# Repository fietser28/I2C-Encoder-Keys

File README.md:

<!--
  SPDX-FileCopyrightText: 2023 Jan Nieuwstad <jan.sources@nieuwstad.net>
  SPDX-License-Identifier: CERN-OHL-W-2.0
-->

# Introduction

This is simple design to connect a rotary encoder with pushbutton and 4 switches to an MCU using I2C. The design uses the common MCP23008 chip. The BOM is kept simple with as many common parts as possible. The encoder and switches have a small RC network in place for basic debouncing (you still need to handle this also in software).

The board breaks out 3V3 power input, GND, SCL, SDA, Interrupt and !Reset.

The board provides pull up resistors for SCL, SDA and the !RESET pin. For each of them there also is a jumper to disable them.

NOTE: The rendering above has an encoder with round shaft, the knob is for an encoder with a D shaped shaft.

This board can be daisy chained. You just have to make sure each board uses a different addres by changing the jumpers A0,A1 and/or A2. Make sure you use the opendrain configuration of the interrupt pin if you want to use interrupts in this case.

# Files

 - The directory I2C-Encoder-Keys contains the KiCad (6) design files.
 - The BOM directory contains an bill of material generated by KiCad
 - 3D contains FreeCad design and 3D printable files (STL) for a case.
 - The root directory contains PDF of the schematic and PCB design.

# License 

This hardware design is under the [CERN Open Hardware Licence Version 2 - Weakly Reciprocal](LICENSES/CERN-OHL-W-4.0.txt)
Illustrations are under the [CERN Open Hardware Licence Version 2 - Weakly Reciprocal](LICENSES/CC-BY-SA-4.0.txt)

This project contains 3D models from others:
- [JST PH connector](https://grabcad.com/library/jst-ph-2-0mm-connector-pack-through-hole-smt-ds1066-1) from Sig Elso <https://grabcad.com/sig.elso-1>
- [Rotary encoder](https://grabcad.com/library/ec11-rotary-encoder-with-switch-1) from Anthony Berkow <https://grabcad.com/anthony.berkow-1>

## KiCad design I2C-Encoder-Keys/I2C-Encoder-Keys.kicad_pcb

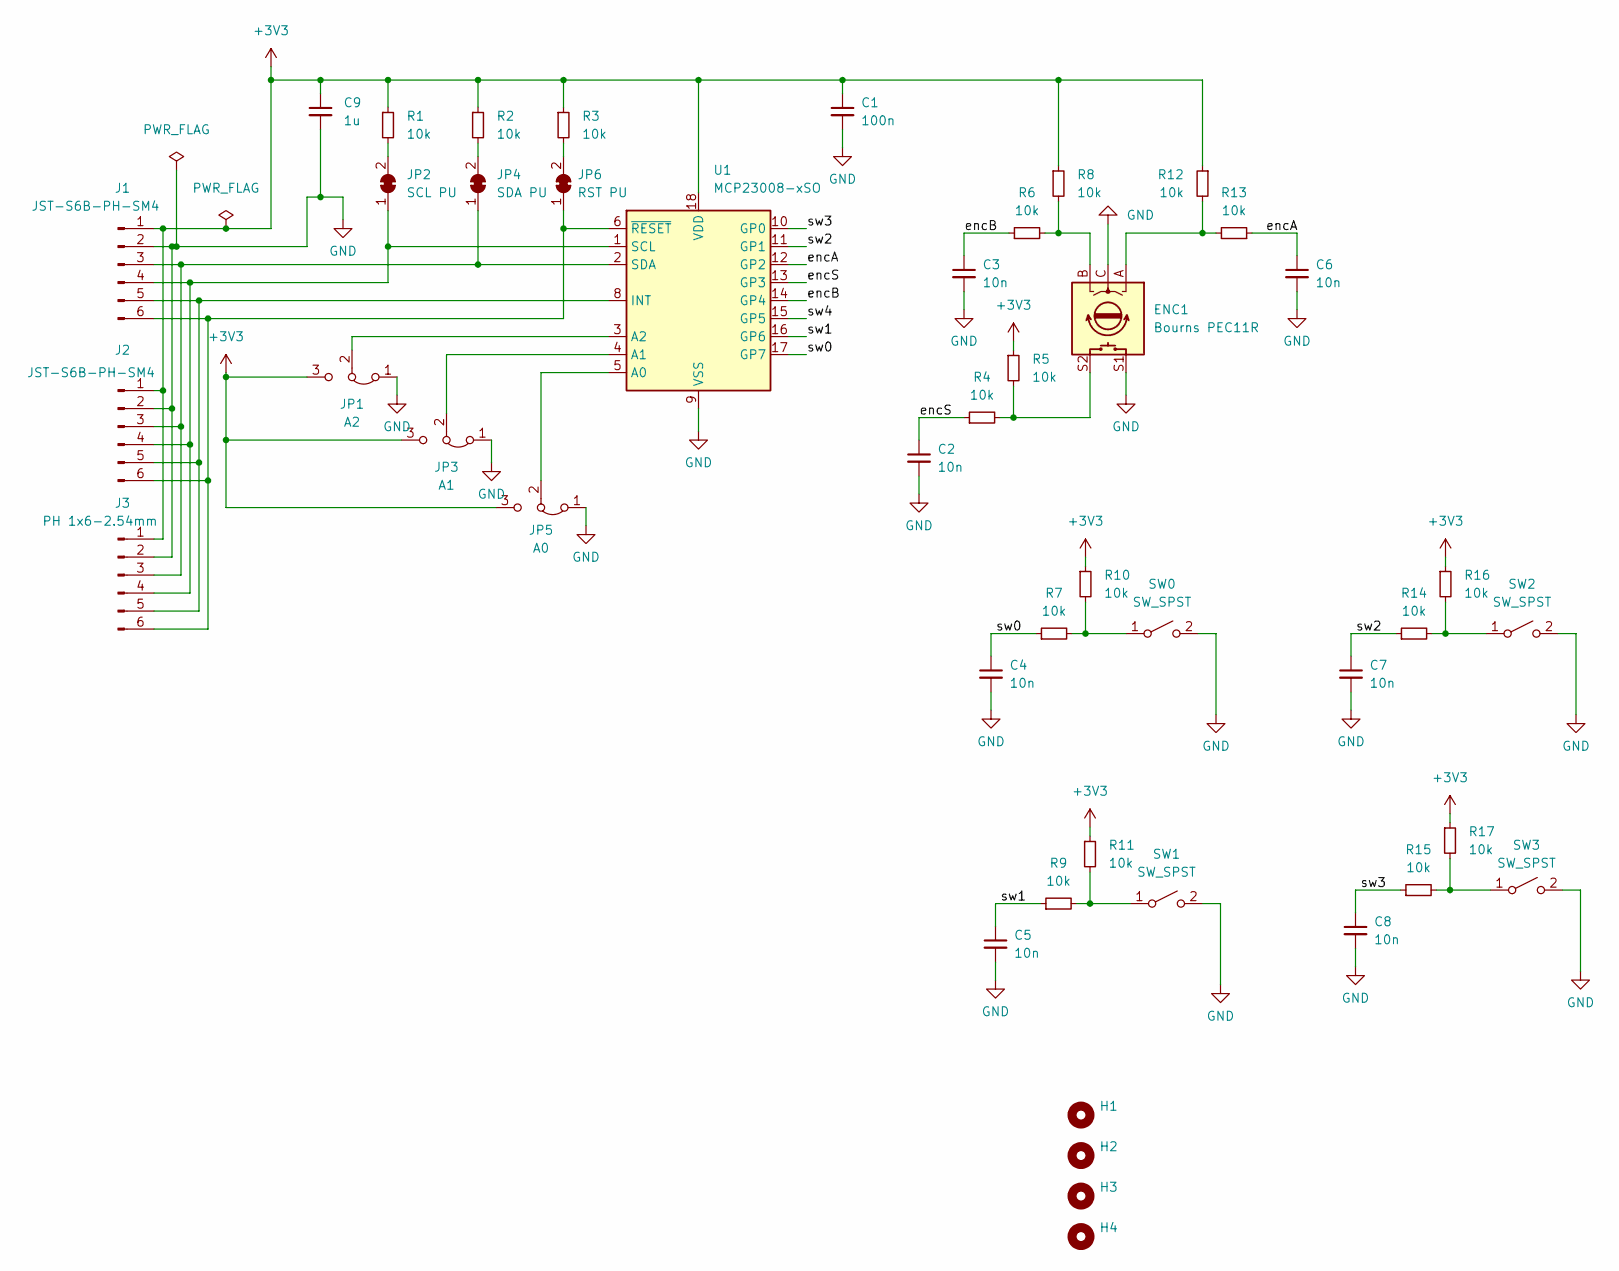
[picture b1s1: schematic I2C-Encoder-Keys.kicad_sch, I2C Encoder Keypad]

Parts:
C1: 100n; C_0805_2012Metric_Pad1.18x1.45mm_HandSolder; LCSC Part # C49678
C2, C3, C4, C5, C6, C7, C8: 10n; C_0805_2012Metric_Pad1.18x1.45mm_HandSolder; LCSC Part # C1710
C9: 1u; C_0805_2012Metric_Pad1.18x1.45mm_HandSolder; LCSC Part # C28323
ENC1: Bourns PEC11R; RotaryEncoder_Alps_EC12E-Switch_Vertical_H20mm
H1, H2, H3, H4: MountingHole; MountingHole_3.2mm_M3_Pad_Via
J1, J2: JST-S6B-PH-SM4; JST_PH_S6B-PH-SM4-TB_1x06-1MP_P2.00mm_Horizontal; LCSC Part # C265405
J3: PH 1x6-2.54mm; PinHeader_1x06_P2.54mm_Vertical
JP1: A2; SolderJumper-3_P1.3mm_Bridged12_RoundedPad1.0x1.5mm
JP2: SCL PU; SolderJumper-2_P1.3mm_Bridged_RoundedPad1.0x1.5mm
JP3: A1; SolderJumper-3_P1.3mm_Bridged12_RoundedPad1.0x1.5mm
JP4: SDA PU; SolderJumper-2_P1.3mm_Bridged_RoundedPad1.0x1.5mm
JP5: A0; SolderJumper-3_P1.3mm_Bridged2Bar12_RoundedPad1.0x1.5mm
JP6: RST PU; SolderJumper-2_P1.3mm_Bridged_RoundedPad1.0x1.5mm
R1, R2, R3, R4, R5, R6, R7, R8, R9, R10, R11, R12, R13, R14, R15, R16, R17: 10k; R_0805_2012Metric_Pad1.20x1.40mm_HandSolder; LCSC Part # C17414
SW0, SW1, SW2, SW3: SW_SPST; SW_PUSH_6mm_H9.5mm
U1: MCP23008-xSO; SOIC-18W_7.5x11.6mm_P1.27mm; LCSC Part # C92253

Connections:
+3V3: C1.1, C9.1, J1.1, J2.1, J3.1, JP1.3 (B), JP3.3 (B), JP5.3 (B), R1.1, R2.1, R3.1, R5.1, R8.1, R10.1, R11.1, R12.1, R16.1, R17.1, U1.18 (VDD)
/encA: C6.1, R13.1, U1.12 (GP2)
/encB: C3.1, R6.1, U1.14 (GP4)
/encS: C2.1, R4.1, U1.13 (GP3)
/sw0: C4.1, R7.1, U1.17 (GP7)
/sw1: C5.1, R9.1, U1.16 (GP6)
/sw2: C7.1, R14.1, U1.11 (GP1)
/sw3: C8.1, R15.1, U1.10 (GP0)
/sw4: U1.15 (GP5)
GND: C1.2, C2.2, C3.2, C4.2, C5.2, C6.2, C7.2, C8.2, C9.2, ENC1.C, ENC1.S1, J1.2, J2.2, J3.2, JP1.1 (A), JP3.1 (A), JP5.1 (A), SW0.2 (B), SW1.2 (B), SW2.2 (B), SW3.2 (B), U1.9 (VSS)
unnamed: ENC1.A, R12.2, R13.2
unnamed: ENC1.B, R6.2, R8.2
unnamed: ENC1.S2, R4.2, R5.2
unnamed: J1.3, J2.3, J3.3, JP4.1 (A), U1.2 (SDA)
unnamed: J1.4, J2.4, J3.4, JP2.1 (A), U1.1 (SCL)
unnamed: J1.5, J2.5, J3.5, U1.8 (INT)
unnamed: J1.6, J2.6, J3.6, JP6.1 (A), U1.6 (~RESET)
unnamed: JP1.2 (C), U1.3 (A2)
unnamed: JP2.2 (B), R1.2
unnamed: JP3.2 (C), U1.4 (A1)
unnamed: JP4.2 (B), R2.2
unnamed: JP5.2 (C), U1.5 (A0)
unnamed: JP6.2 (B), R3.2
unnamed: R7.2, R10.2, SW0.1 (A)
unnamed: R9.2, R11.2, SW1.1 (A)
unnamed: R14.2, R16.2, SW2.1 (A)
unnamed: R15.2, R17.2, SW3.1 (A)

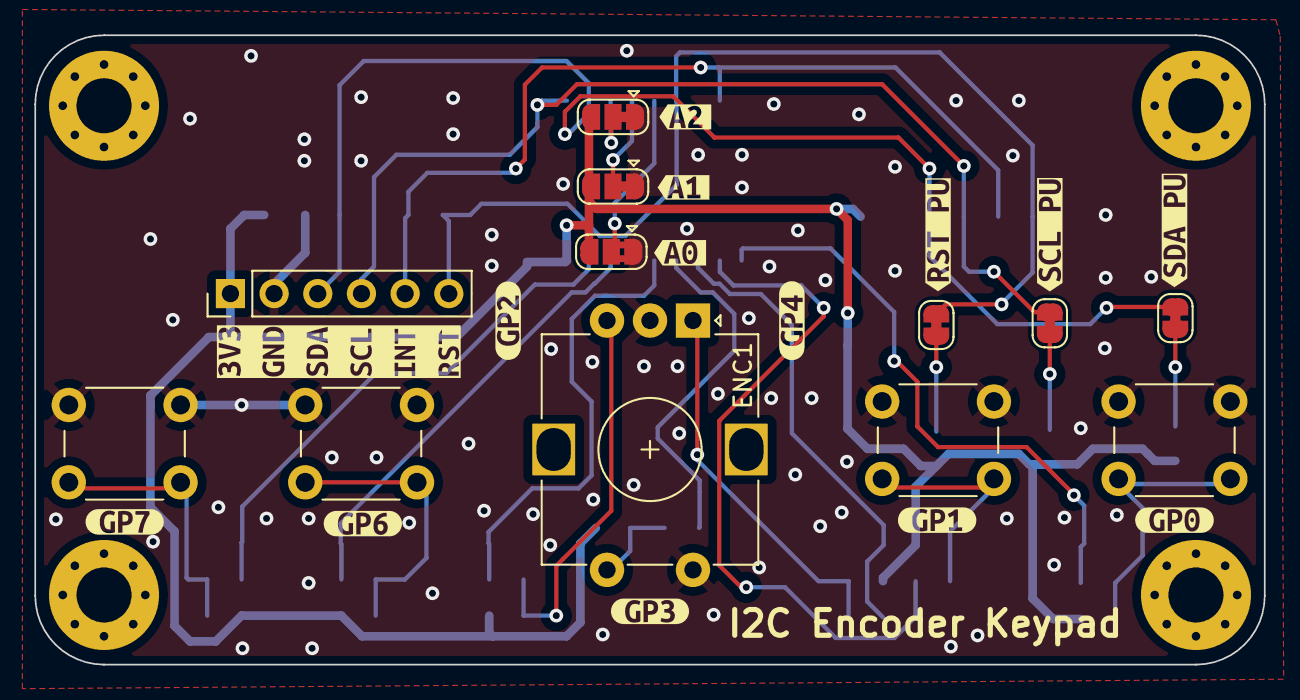
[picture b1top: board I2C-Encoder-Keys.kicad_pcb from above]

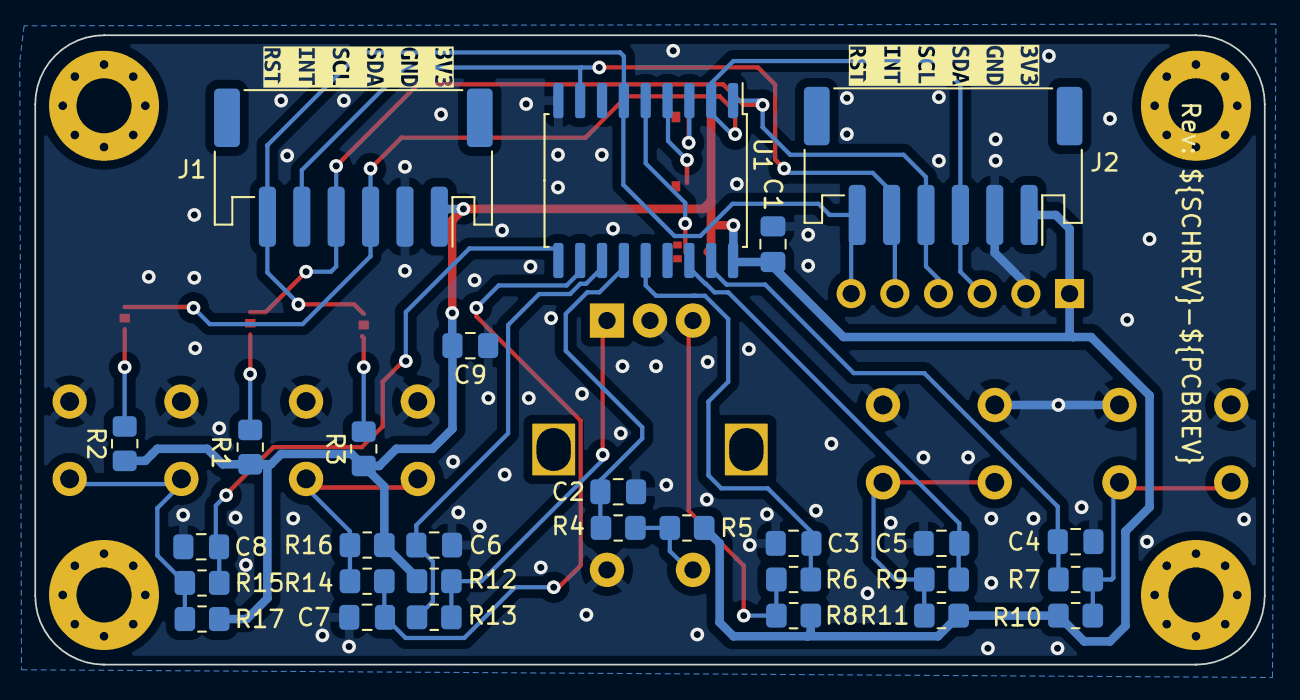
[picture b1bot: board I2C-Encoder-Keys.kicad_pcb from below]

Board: 2 copper layers, 71.5 x 36.6 mm, 61 parts (31 on the bottom side), 26 nets.

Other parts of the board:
kibuzzard-63ABAB39: G***; kibuzzard-63ABAB39
kibuzzard-63ABAB54: G***; kibuzzard-63ABAB54
kibuzzard-63ABAB66: G***; kibuzzard-63ABAB66
kibuzzard-63ABAFD8: G***; kibuzzard-63ABAFD8
kibuzzard-63ABB001: G***; kibuzzard-63ABB001
kibuzzard-63ABB1F4: G***; kibuzzard-63ABB1F4
kibuzzard-63ABB06A: G***; kibuzzard-63ABB06A
kibuzzard-63ABB13E: G***; kibuzzard-63ABB13E
kibuzzard-63ABB15D: G***; kibuzzard-63ABB15D
kibuzzard-63ABB22D: G***; kibuzzard-63ABB22D
kibuzzard-63ABB036: G***; kibuzzard-63ABB036
kibuzzard-63ABB131: G***; kibuzzard-63ABB131
kibuzzard-63ABB252: G***; kibuzzard-63ABB252
kibuzzard-63ADADA8: G***; kibuzzard-63ADADA8
kibuzzard-63ADBF96, kibuzzard-63ADBF96#2: G***; kibuzzard-63ADBF96

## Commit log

2022-12-29 initial commit - v1.0-A
2023-01-08 Added encoder knob
2023-01-09 Added photo
2023-01-11 Small update to text/git.
2023-01-11 Removed work in progress statement. It works. :-)
2023-01-11 Fixed .gitignore and removed FreeCad backupfile
2023-09-01 License cleanup
2023-09-01 typos
2023-09-01 workflow fix & license cleanup
